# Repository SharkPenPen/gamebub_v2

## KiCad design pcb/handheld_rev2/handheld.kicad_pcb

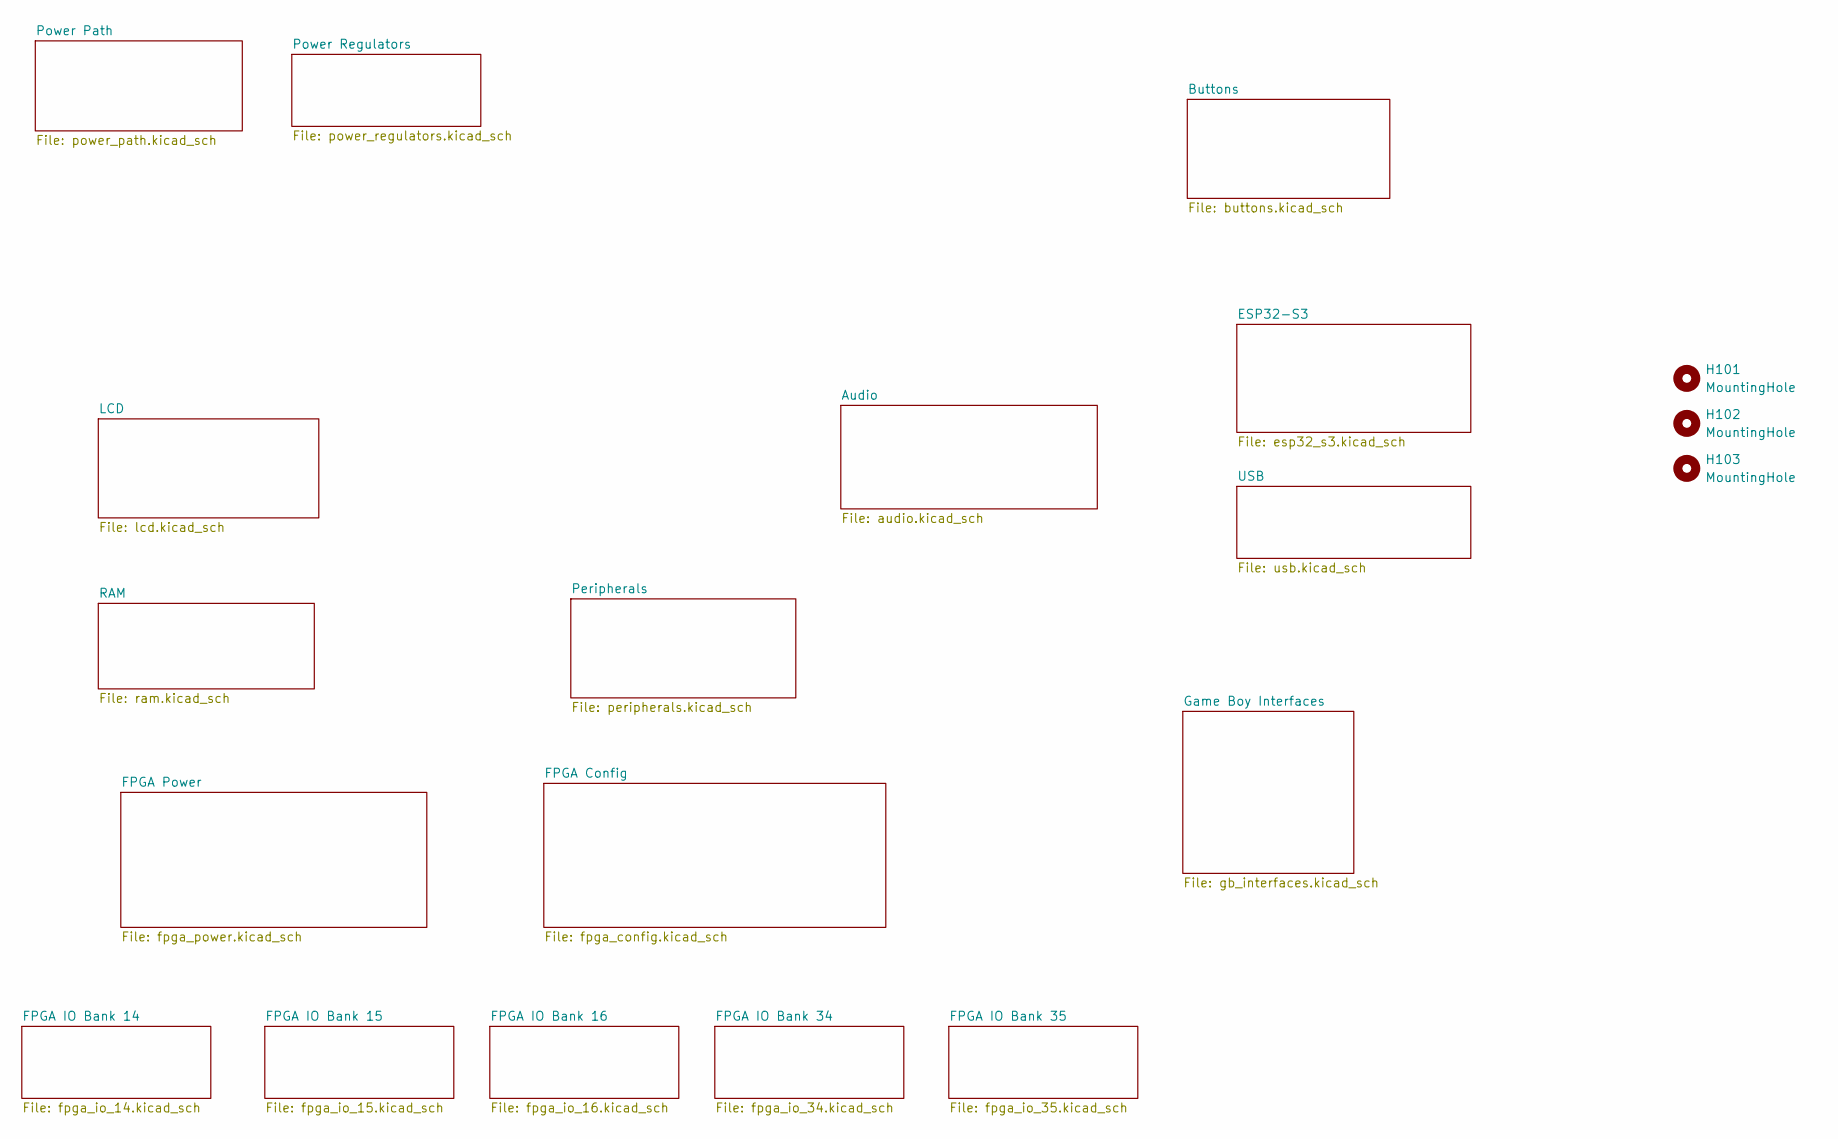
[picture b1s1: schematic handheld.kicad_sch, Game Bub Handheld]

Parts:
H101, H102, H103: MountingHole; MountingHole_2.7mm_M2.5

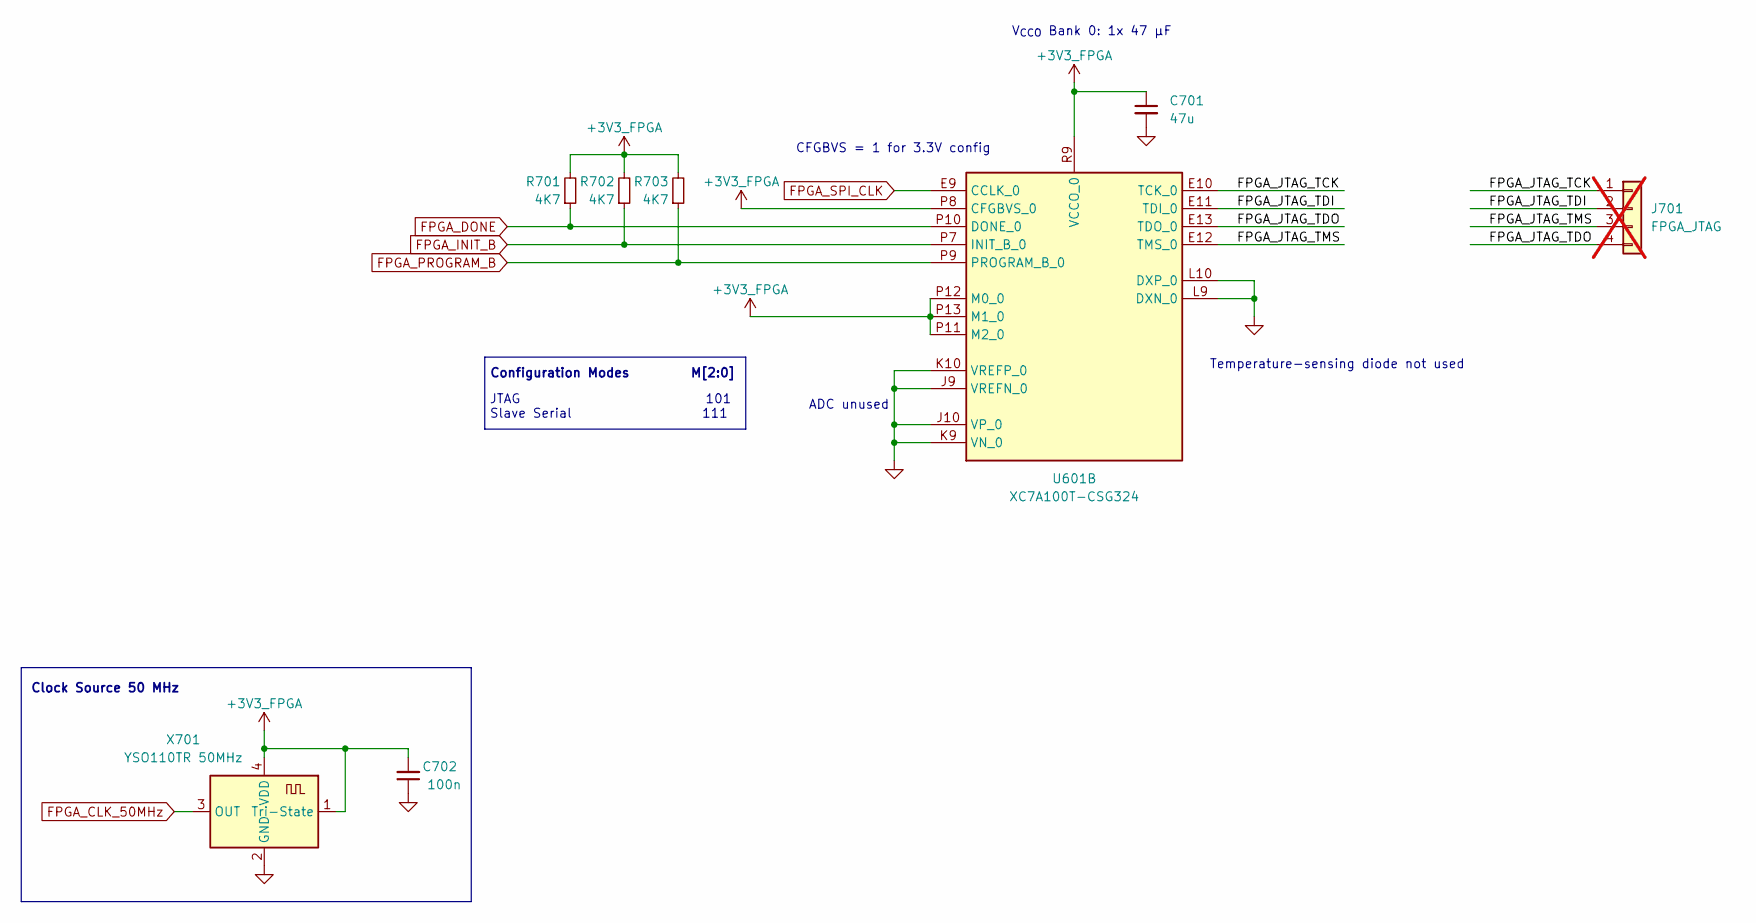
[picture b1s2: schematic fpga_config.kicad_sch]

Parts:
C701: 47u; C_0805_2012Metric; LCSC C16780
C702: 100n; C_0402_1005Metric; LCSC C1525
J701: FPGA_JTAG; PinSocket_1x04_P2.54mm_Vertical; not fitted
R701, R702, R703: 4K7; R_0402_1005Metric; LCSC C25900
U601: XC7A100T-CSG324; Xilinx_CSG324; LCSC C1521791
X701: YSO110TR 50MHz; Oscillator_SMD_SeikoEpson_SG8002CE-4Pin_3.2x2.5mm; LCSC C5203552

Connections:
+3V3_FPGA: C701.1, C702.2, R701.2, R702.2, R703.2, U601.P8 (CFGBVS_0), U601.P11 (M2_0), U601.P12 (M0_0), U601.P13 (M1_0), U601.R9 (VCCO_0), X701.1 (Tri-State), X701.4 (VDD); also elsewhere on the board
/FPGA Config/FPGA_JTAG_TCK: J701.1, U601.E10 (TCK_0)
/FPGA Config/FPGA_JTAG_TDI: J701.2, U601.E11 (TDI_0)
/FPGA Config/FPGA_JTAG_TDO: J701.4, U601.E13 (TDO_0)
/FPGA Config/FPGA_JTAG_TMS: J701.3, U601.E12 (TMS_0)
FPGA_CLK_50MHz: X701.3 (OUT); also elsewhere on the board
FPGA_DONE: R701.1, U601.P10 (DONE_0); also elsewhere on the board
FPGA_INIT_B: R702.1, U601.P7 (INIT_B_0); also elsewhere on the board
FPGA_PROGRAM_B: R703.1, U601.P9 (PROGRAM_B_0); also elsewhere on the board
FPGA_SPI_CLK: U601.E9 (CCLK_0); also elsewhere on the board
GND: C701.2, C702.1, U601.J9 (VREFN_0), U601.J10 (VP_0), U601.K9 (VN_0), U601.K10 (VREFP_0), U601.L9 (DXN_0), U601.L10 (DXP_0), X701.2 (GND); also elsewhere on the board

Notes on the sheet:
Clock Source 50 MHz
JTAG 101 Slave Serial 111
V_{CCO} Bank 0: 1x 47 µF
ADC unused
CFGBVS = 1 for 3.3V config
Temperature-sensing diode not used
Configuration Modes M[2:0]

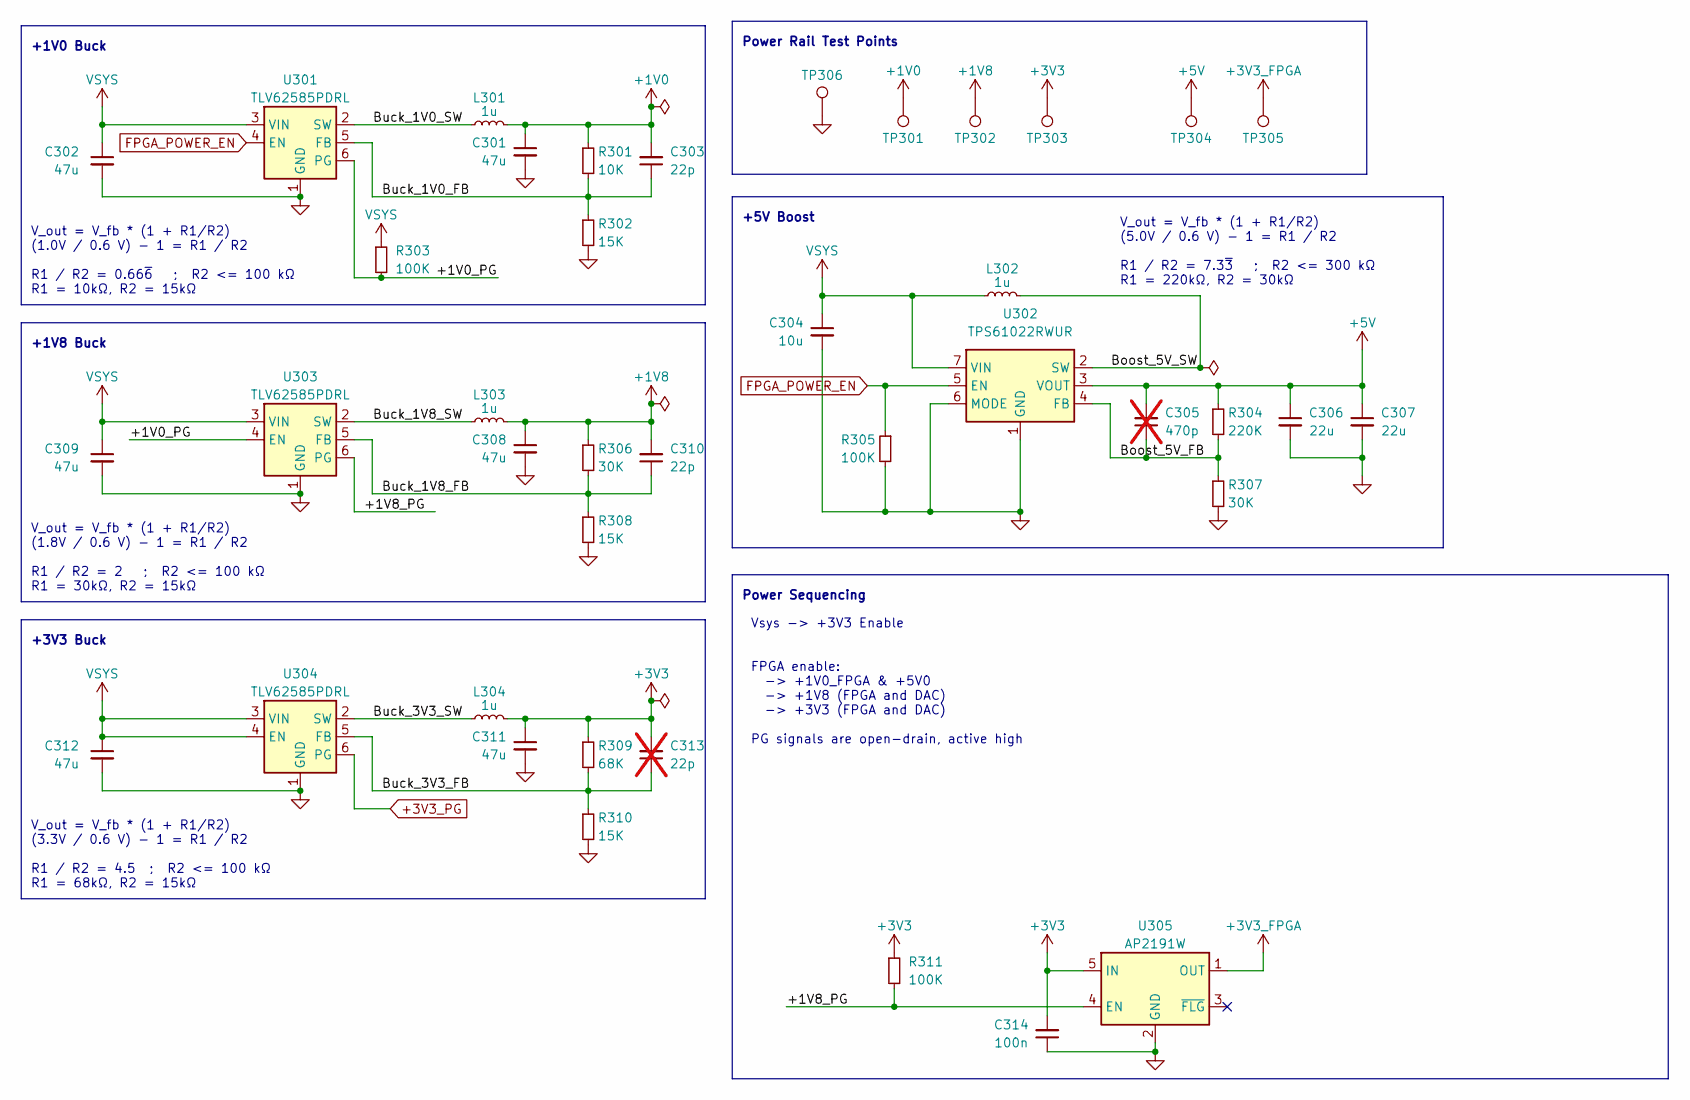
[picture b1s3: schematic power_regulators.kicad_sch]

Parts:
C301, C302, C308, C309, C311, C312: 47u; C_0805_2012Metric; LCSC C16780
C303, C310: 22p; C_0402_1005Metric; LCSC C1555
C304: 10u; C_0402_1005Metric; LCSC C15525
C305: 470p; C_0402_1005Metric; LCSC C1537; not fitted
C306, C307: 22u; C_0805_2012Metric; LCSC C45783
C313: 22p; C_0402_1005Metric; LCSC C1555; not fitted
C314: 100n; C_0402_1005Metric; LCSC C1525
L301, L302, L303, L304: 1u; L_Sunlord_SWPA252012S; LCSC C98348
R301: 10K; R_0402_1005Metric; LCSC C25744
R302, R308, R310: 15K; R_0402_1005Metric; LCSC C25756
R303, R305, R311: 100K; R_0402_1005Metric; LCSC C25741
R304: 220K; R_0603_1608Metric; LCSC C22961
R306, R307: 30K; R_0402_1005Metric; LCSC C25776
R309: 68K; R_0402_1005Metric; LCSC C36871
TP301: +1V0; TestPoint_2.54mm_THT
TP302: +1V8; TestPoint_2.54mm_THT
TP303: +3V3; TestPoint_2.54mm_THT
TP304: +5V; TestPoint_2.54mm_THT
TP305: +3V3_FPGA; TestPoint_2.54mm_THT
TP306: GND; TestPoint_2.54mm_THT
U301, U303, U304: TLV62585PDRL; SOT-563; LCSC C485118
U302: TPS61022RWUR; VQFN-7_L2.0-W2.0-P0.55-TL_RWU; LCSC C915088
U305: AP2191W; SOT-23-5; LCSC C141321

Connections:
+1V0: C301.1, C303.2, L301.2, R301.1, TP301.1; also elsewhere on the board
+1V8: C308.1, C310.2, L303.2, R306.1, TP302.1; also elsewhere on the board
+3V3: C311.1, C313.2, C314.2, L304.2, R309.1, R311.1, TP303.1, U305.5 (IN); also elsewhere on the board
+3V3_FPGA: TP305.1, U305.1 (OUT); also elsewhere on the board
+3V3_PG: U304.6 (PG); also elsewhere on the board
+5V: C305.2, C306.1, C307.1, R304.1, TP304.1, U302.3 (VOUT); also elsewhere on the board
/Power Regulators/+1V0_PG: R303.2, U301.6 (PG), U303.4 (EN)
/Power Regulators/+1V8_PG: R311.2, U303.6 (PG), U305.4 (EN)
/Power Regulators/Boost_5V_FB: C305.1, R304.2, R307.1, U302.4 (FB)
/Power Regulators/Boost_5V_SW: L302.2, U302.2 (SW)
/Power Regulators/Buck_1V0_FB: C303.1, R301.2, R302.1, U301.5 (FB)
/Power Regulators/Buck_1V0_SW: L301.1, U301.2 (SW)
/Power Regulators/Buck_1V8_FB: C310.1, R306.2, R308.1, U303.5 (FB)
/Power Regulators/Buck_1V8_SW: L303.1, U303.2 (SW)
/Power Regulators/Buck_3V3_FB: C313.1, R309.2, R310.1, U304.5 (FB)
/Power Regulators/Buck_3V3_SW: L304.1, U304.2 (SW)
FPGA_POWER_EN: R305.1, U301.4 (EN), U302.5 (EN); also elsewhere on the board
GND: C301.2, C302.2, C304.2, C306.2, C307.2, C308.2, C309.2, C311.2, C312.2, C314.1, R302.2, R305.2, R307.2, R308.2, R310.2, TP306.1, U301.1 (GND), U302.1 (GND), U302.6 (MODE), U303.1 (GND), U304.1 (GND), U305.2 (GND); also elsewhere on the board
VSYS: C302.1, C304.1, C309.1, C312.1, L302.1, R303.1, U301.3 (VIN), U302.7 (VIN), U303.3 (VIN), U304.3 (VIN), U304.4 (EN); also elsewhere on the board

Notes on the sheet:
+1V8 Buck
V_out = V_fb * (1 + R1/R2) (5.0V / 0.6 V) - 1 = R1 / R2 R1 / R2 = 7.3~{3} ; R2 <= 300 kΩ R1 = 220kΩ, R2 = 30kΩ
V_out = V_fb * (1 + R1/R2) (3.3V / 0.6 V) - 1 = R1 / R2 R1 / R2 = 4.5 ; R2 <= 100 kΩ R1 = 68kΩ, R2 = 15kΩ
+1V0 Buck
V_out = V_fb * (1 + R1/R2) (1.8V / 0.6 V) - 1 = R1 / R2 R1 / R2 = 2 ; R2 <= 100 kΩ R1 = 30kΩ, R2 = 15kΩ
Vsys -> +3V3 Enable FPGA enable: -> +1V0_FPGA & +5V0 -> +1V8 (FPGA and DAC) -> +3V3 (FPGA and DAC) PG signals are open-drain, active high
Power Rail Test Points
Power Sequencing
V_out = V_fb * (1 + R1/R2) (1.0V / 0.6 V) - 1 = R1 / R2 R1 / R2 = 0.66~{6} ; R2 <= 100 kΩ R1 = 10kΩ, R2 = 15kΩ
+3V3 Buck
+5V Boost

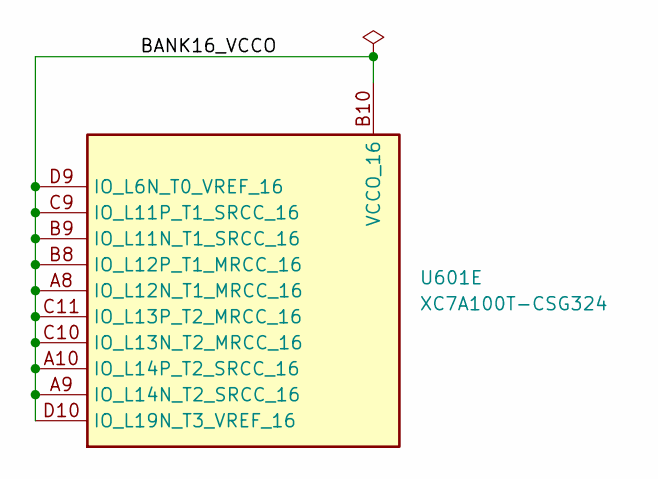
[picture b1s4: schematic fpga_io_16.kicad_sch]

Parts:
U601: XC7A100T-CSG324; Xilinx_CSG324; LCSC C1521791

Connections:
/FPGA IO Bank 16/BANK16_VCCO: U601.A8 (IO_L12N_T1_MRCC_16), U601.A9 (IO_L14N_T2_SRCC_16), U601.A10 (IO_L14P_T2_SRCC_16), U601.B8 (IO_L12P_T1_MRCC_16), U601.B9 (IO_L11N_T1_SRCC_16), U601.B10 (VCCO_16), U601.C9 (IO_L11P_T1_SRCC_16), U601.C10 (IO_L13N_T2_MRCC_16), U601.C11 (IO_L13P_T2_MRCC_16), U601.D9 (IO_L6N_T0_VREF_16), U601.D10 (IO_L19N_T3_VREF_16)

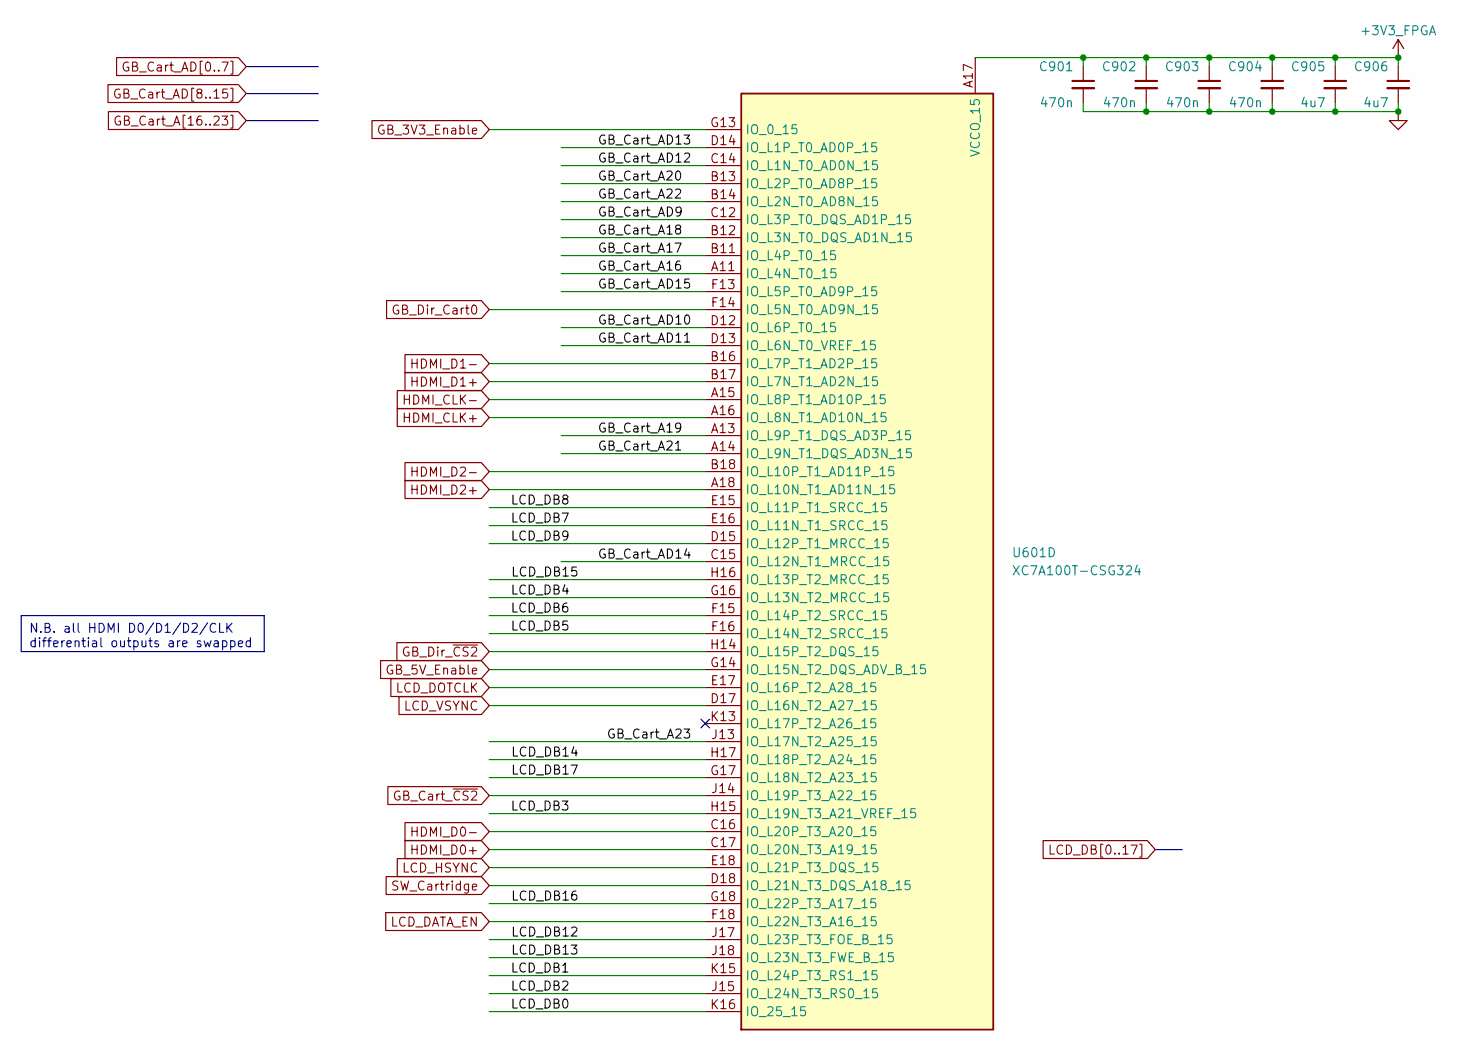
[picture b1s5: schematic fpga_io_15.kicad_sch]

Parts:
C901, C902, C903, C904: 470n; C_0402_1005Metric; LCSC C47339
C905, C906: 4u7; C_0402_1005Metric; LCSC C23733
U601: XC7A100T-CSG324; Xilinx_CSG324; LCSC C1521791

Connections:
+3V3_FPGA: C901.1, C902.1, C903.1, C904.1, C905.1, C906.1, U601.A17 (VCCO_15), U601.C13 (VCCO_15), U601.D16 (VCCO_15), U601.G15 (VCCO_15), U601.H18 (VCCO_15), U601.K14 (VCCO_15); also elsewhere on the board
GB_3V3_Enable: U601.G13 (IO_0_15); also elsewhere on the board
GB_5V_Enable: U601.G14 (IO_L15N_T2_DQS_ADV_B_15); also elsewhere on the board
GB_Cart_A16: U601.A11 (IO_L4N_T0_15); also elsewhere on the board
GB_Cart_A17: U601.B11 (IO_L4P_T0_15); also elsewhere on the board
GB_Cart_A18: U601.B12 (IO_L3N_T0_DQS_AD1N_15); also elsewhere on the board
GB_Cart_A19: U601.A13 (IO_L9P_T1_DQS_AD3P_15); also elsewhere on the board
GB_Cart_A20: U601.B13 (IO_L2P_T0_AD8P_15); also elsewhere on the board
GB_Cart_A21: U601.A14 (IO_L9N_T1_DQS_AD3N_15); also elsewhere on the board
GB_Cart_A22: U601.B14 (IO_L2N_T0_AD8N_15); also elsewhere on the board
GB_Cart_A23: U601.J13 (IO_L17N_T2_A25_15); also elsewhere on the board
GB_Cart_AD9: U601.C12 (IO_L3P_T0_DQS_AD1P_15); also elsewhere on the board
GB_Cart_AD10: U601.D12 (IO_L6P_T0_15); also elsewhere on the board
GB_Cart_AD11: U601.D13 (IO_L6N_T0_VREF_15); also elsewhere on the board
GB_Cart_AD12: U601.C14 (IO_L1N_T0_AD0N_15); also elsewhere on the board
GB_Cart_AD13: U601.D14 (IO_L1P_T0_AD0P_15); also elsewhere on the board
GB_Cart_AD14: U601.C15 (IO_L12N_T1_MRCC_15); also elsewhere on the board
GB_Cart_AD15: U601.F13 (IO_L5P_T0_AD9P_15); also elsewhere on the board
GB_Cart_~CS2: U601.J14 (IO_L19P_T3_A22_15); also elsewhere on the board
GB_Dir_Cart0: U601.F14 (IO_L5N_T0_AD9N_15); also elsewhere on the board
GB_Dir_~CS2: U601.H14 (IO_L15P_T2_DQS_15); also elsewhere on the board
GND: C901.2, C902.2, C903.2, C904.2, C905.2, C906.2; also elsewhere on the board
HDMI_CLK+: U601.A16 (IO_L8N_T1_AD10N_15); also elsewhere on the board
HDMI_CLK-: U601.A15 (IO_L8P_T1_AD10P_15); also elsewhere on the board
HDMI_D0+: U601.C17 (IO_L20N_T3_A19_15); also elsewhere on the board
HDMI_D0-: U601.C16 (IO_L20P_T3_A20_15); also elsewhere on the board
HDMI_D1+: U601.B17 (IO_L7N_T1_AD2N_15); also elsewhere on the board
HDMI_D1-: U601.B16 (IO_L7P_T1_AD2P_15); also elsewhere on the board
HDMI_D2+: U601.A18 (IO_L10N_T1_AD11N_15); also elsewhere on the board
HDMI_D2-: U601.B18 (IO_L10P_T1_AD11P_15); also elsewhere on the board
LCD_DATA_EN: U601.F18 (IO_L22N_T3_A16_15); also elsewhere on the board
LCD_DB0: U601.K16 (IO_25_15); also elsewhere on the board
LCD_DB1: U601.K15 (IO_L24P_T3_RS1_15); also elsewhere on the board
LCD_DB2: U601.J15 (IO_L24N_T3_RS0_15); also elsewhere on the board
LCD_DB3: U601.H15 (IO_L19N_T3_A21_VREF_15); also elsewhere on the board
LCD_DB4: U601.G16 (IO_L13N_T2_MRCC_15); also elsewhere on the board
LCD_DB5: U601.F16 (IO_L14N_T2_SRCC_15); also elsewhere on the board
LCD_DB6: U601.F15 (IO_L14P_T2_SRCC_15); also elsewhere on the board
LCD_DB7: U601.E16 (IO_L11N_T1_SRCC_15); also elsewhere on the board
LCD_DB8: U601.E15 (IO_L11P_T1_SRCC_15); also elsewhere on the board
LCD_DB9: U601.D15 (IO_L12P_T1_MRCC_15); also elsewhere on the board
LCD_DB12: U601.J17 (IO_L23P_T3_FOE_B_15); also elsewhere on the board
LCD_DB13: U601.J18 (IO_L23N_T3_FWE_B_15); also elsewhere on the board
LCD_DB14: U601.H17 (IO_L18P_T2_A24_15); also elsewhere on the board
LCD_DB15: U601.H16 (IO_L13P_T2_MRCC_15); also elsewhere on the board
LCD_DB16: U601.G18 (IO_L22P_T3_A17_15); also elsewhere on the board
LCD_DB17: U601.G17 (IO_L18N_T2_A23_15); also elsewhere on the board
LCD_DOTCLK: U601.E17 (IO_L16P_T2_A28_15); also elsewhere on the board
LCD_HSYNC: U601.E18 (IO_L21P_T3_DQS_15); also elsewhere on the board
LCD_VSYNC: U601.D17 (IO_L16N_T2_A27_15); also elsewhere on the board
SW_Cartridge: U601.D18 (IO_L21N_T3_DQS_A18_15); also elsewhere on the board

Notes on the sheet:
N.B. all HDMI D0/D1/D2/CLK differential outputs are swapped

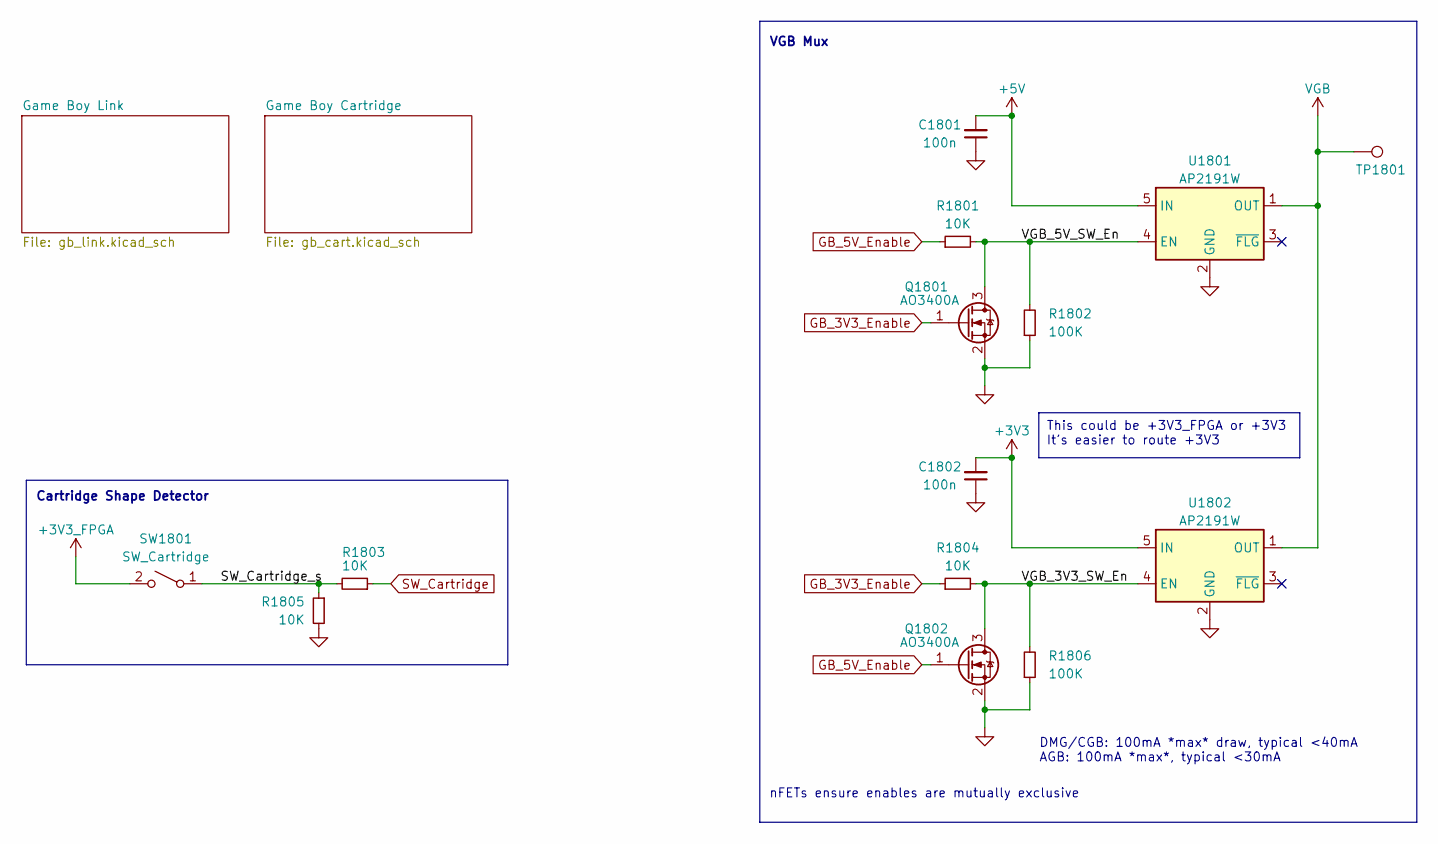
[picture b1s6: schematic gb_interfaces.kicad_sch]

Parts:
C1801, C1802: 100n; C_0402_1005Metric; LCSC C1525
Q1801, Q1802: AO3400A; SOT-23; LCSC C20917
R1801, R1803, R1804, R1805: 10K; R_0402_1005Metric; LCSC C25744
R1802, R1806: 100K; R_0402_1005Metric; LCSC C25741
SW1801: SW_Cartridge; JJOV0UL650NONPRBK_SIDE
TP1801: VGB; TestPoint_2.54mm_THT
U1801, U1802: AP2191W; SOT-23-5; LCSC C141321

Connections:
+3V3: C1802.2, U1802.5 (IN); also elsewhere on the board
+3V3_FPGA: SW1801.2 (B); also elsewhere on the board
+5V: C1801.2, U1801.5 (IN); also elsewhere on the board
/Game Boy Interfaces/SW_Cartridge_s: R1803.2, R1805.1, SW1801.1 (A)
/Game Boy Interfaces/VGB_3V3_SW_En: Q1802.3 (D), R1804.2, R1806.2, U1802.4 (EN)
/Game Boy Interfaces/VGB_5V_SW_En: Q1801.3 (D), R1801.2, R1802.2, U1801.4 (EN)
GB_3V3_Enable: Q1801.1 (G), R1804.1; also elsewhere on the board
GB_5V_Enable: Q1802.1 (G), R1801.1; also elsewhere on the board
GND: C1801.1, C1802.1, Q1801.2 (S), Q1802.2 (S), R1802.1, R1805.2, R1806.1, U1801.2 (GND), U1802.2 (GND); also elsewhere on the board
SW_Cartridge: R1803.1; also elsewhere on the board
VGB: TP1801.1, U1801.1 (OUT), U1802.1 (OUT); also elsewhere on the board

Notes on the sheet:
This could be +3V3_FPGA or +3V3 It's easier to route +3V3
DMG/CGB: 100mA *max* draw, typical <40mA AGB: 100mA *max*, typical <30mA
Cartridge Shape Detector
VGB Mux
nFETs ensure enables are mutually exclusive

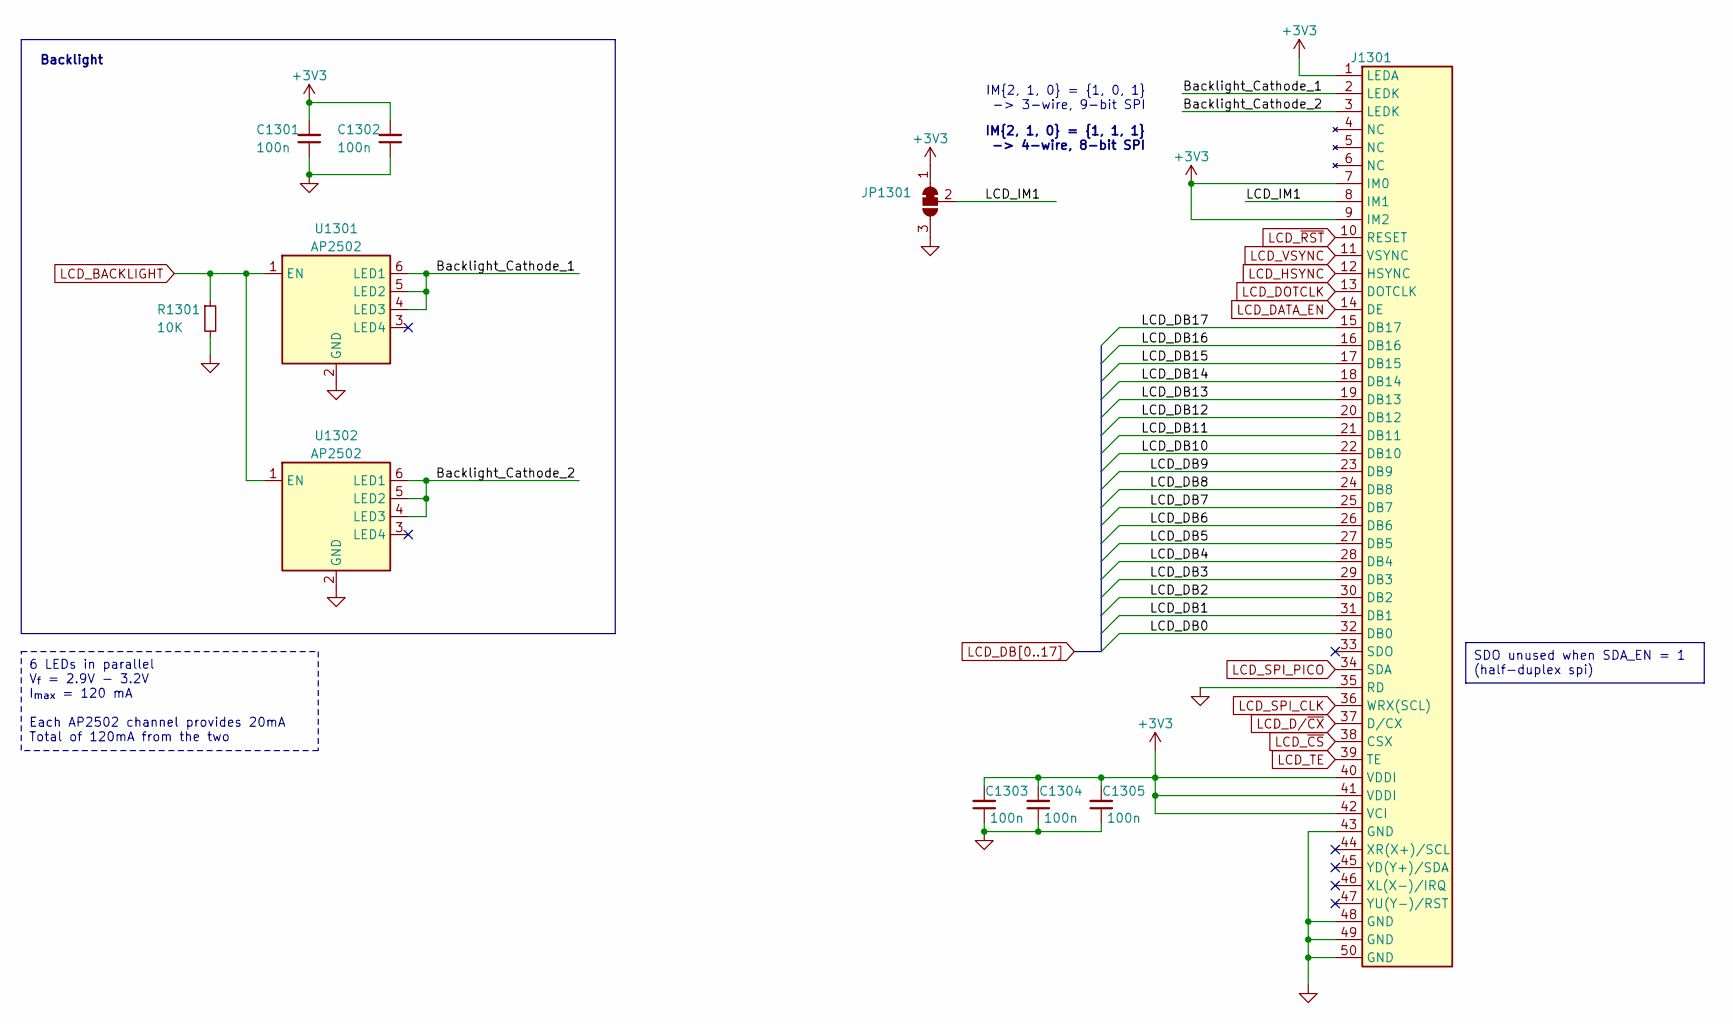
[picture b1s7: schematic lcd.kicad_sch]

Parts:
C1301, C1302, C1303, C1304, C1305: 100n; C_0402_1005Metric; LCSC C1525
J1301: Hirose_FH12S-50S-0.5SH_1x50-1MP_P0.50mm_Horizontal_FLIPPED; LCSC C598003
JP1301: SolderJumper_3_Bridged12; SolderJumper-3_P1.3mm_Bridged12_RoundedPad1.0x1.5mm
R1301: 10K; R_0402_1005Metric; LCSC C25744
U1301, U1302: AP2502; SOT-23-6; LCSC C460349

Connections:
+3V3: C1301.2, C1302.2, C1303.2, C1304.2, C1305.2, J1301.1 (LEDA), J1301.7 (IM0), J1301.9 (IM2), J1301.40 (VDDI), J1301.41 (VDDI), J1301.42 (VCI), JP1301.1 (A); also elsewhere on the board
/LCD/Backlight_Cathode_1: J1301.2 (LEDK), U1301.4 (LED3), U1301.5 (LED2), U1301.6 (LED1)
/LCD/Backlight_Cathode_2: J1301.3 (LEDK), U1302.4 (LED3), U1302.5 (LED2), U1302.6 (LED1)
/LCD/LCD_IM1: J1301.8 (IM1), JP1301.2 (C)
GND: C1301.1, C1302.1, C1303.1, C1304.1, C1305.1, J1301.35 (RD), J1301.43 (GND), J1301.48 (GND), J1301.49 (GND), J1301.50 (GND), JP1301.3 (B), R1301.2, U1301.2 (GND), U1302.2 (GND); also elsewhere on the board
LCD_BACKLIGHT: R1301.1, U1301.1 (EN), U1302.1 (EN); also elsewhere on the board
LCD_DATA_EN: J1301.14 (DE); also elsewhere on the board
LCD_DB0: J1301.32 (DB0); also elsewhere on the board
LCD_DB1: J1301.31 (DB1); also elsewhere on the board
LCD_DB2: J1301.30 (DB2); also elsewhere on the board
LCD_DB3: J1301.29 (DB3); also elsewhere on the board
LCD_DB4: J1301.28 (DB4); also elsewhere on the board
LCD_DB5: J1301.27 (DB5); also elsewhere on the board
LCD_DB6: J1301.26 (DB6); also elsewhere on the board
LCD_DB7: J1301.25 (DB7); also elsewhere on the board
LCD_DB8: J1301.24 (DB8); also elsewhere on the board
LCD_DB9: J1301.23 (DB9); also elsewhere on the board
LCD_DB10: J1301.22 (DB10); also elsewhere on the board
LCD_DB11: J1301.21 (DB11); also elsewhere on the board
LCD_DB12: J1301.20 (DB12); also elsewhere on the board
LCD_DB13: J1301.19 (DB13); also elsewhere on the board
LCD_DB14: J1301.18 (DB14); also elsewhere on the board
LCD_DB15: J1301.17 (DB15); also elsewhere on the board
LCD_DB16: J1301.16 (DB16); also elsewhere on the board
LCD_DB17: J1301.15 (DB17); also elsewhere on the board
LCD_DOTCLK: J1301.13 (DOTCLK); also elsewhere on the board
LCD_D/~CX: J1301.37 (D/CX); also elsewhere on the board
LCD_HSYNC: J1301.12 (HSYNC); also elsewhere on the board
LCD_SPI_CLK: J1301.36 (WRX(SCL)); also elsewhere on the board
LCD_SPI_PICO: J1301.34 (SDA); also elsewhere on the board
LCD_TE: J1301.39 (TE); also elsewhere on the board
LCD_VSYNC: J1301.11 (VSYNC); also elsewhere on the board
LCD_~CS: J1301.38 (CSX); also elsewhere on the board
LCD_~RST: J1301.10 (RESET); also elsewhere on the board

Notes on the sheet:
SDO unused when SDA_EN = 1 (half-duplex spi)
6 LEDs in parallel V_{f} = 2.9V - 3.2V I_{max} = 120 mA Each AP2502 channel provides 20mA Total of 120mA from the two
Backlight
IM{2, 1, 0} = {1, 1, 1} -> 4-wire, 8-bit SPI
IM{2, 1, 0} = {1, 0, 1} -> 3-wire, 9-bit SPI

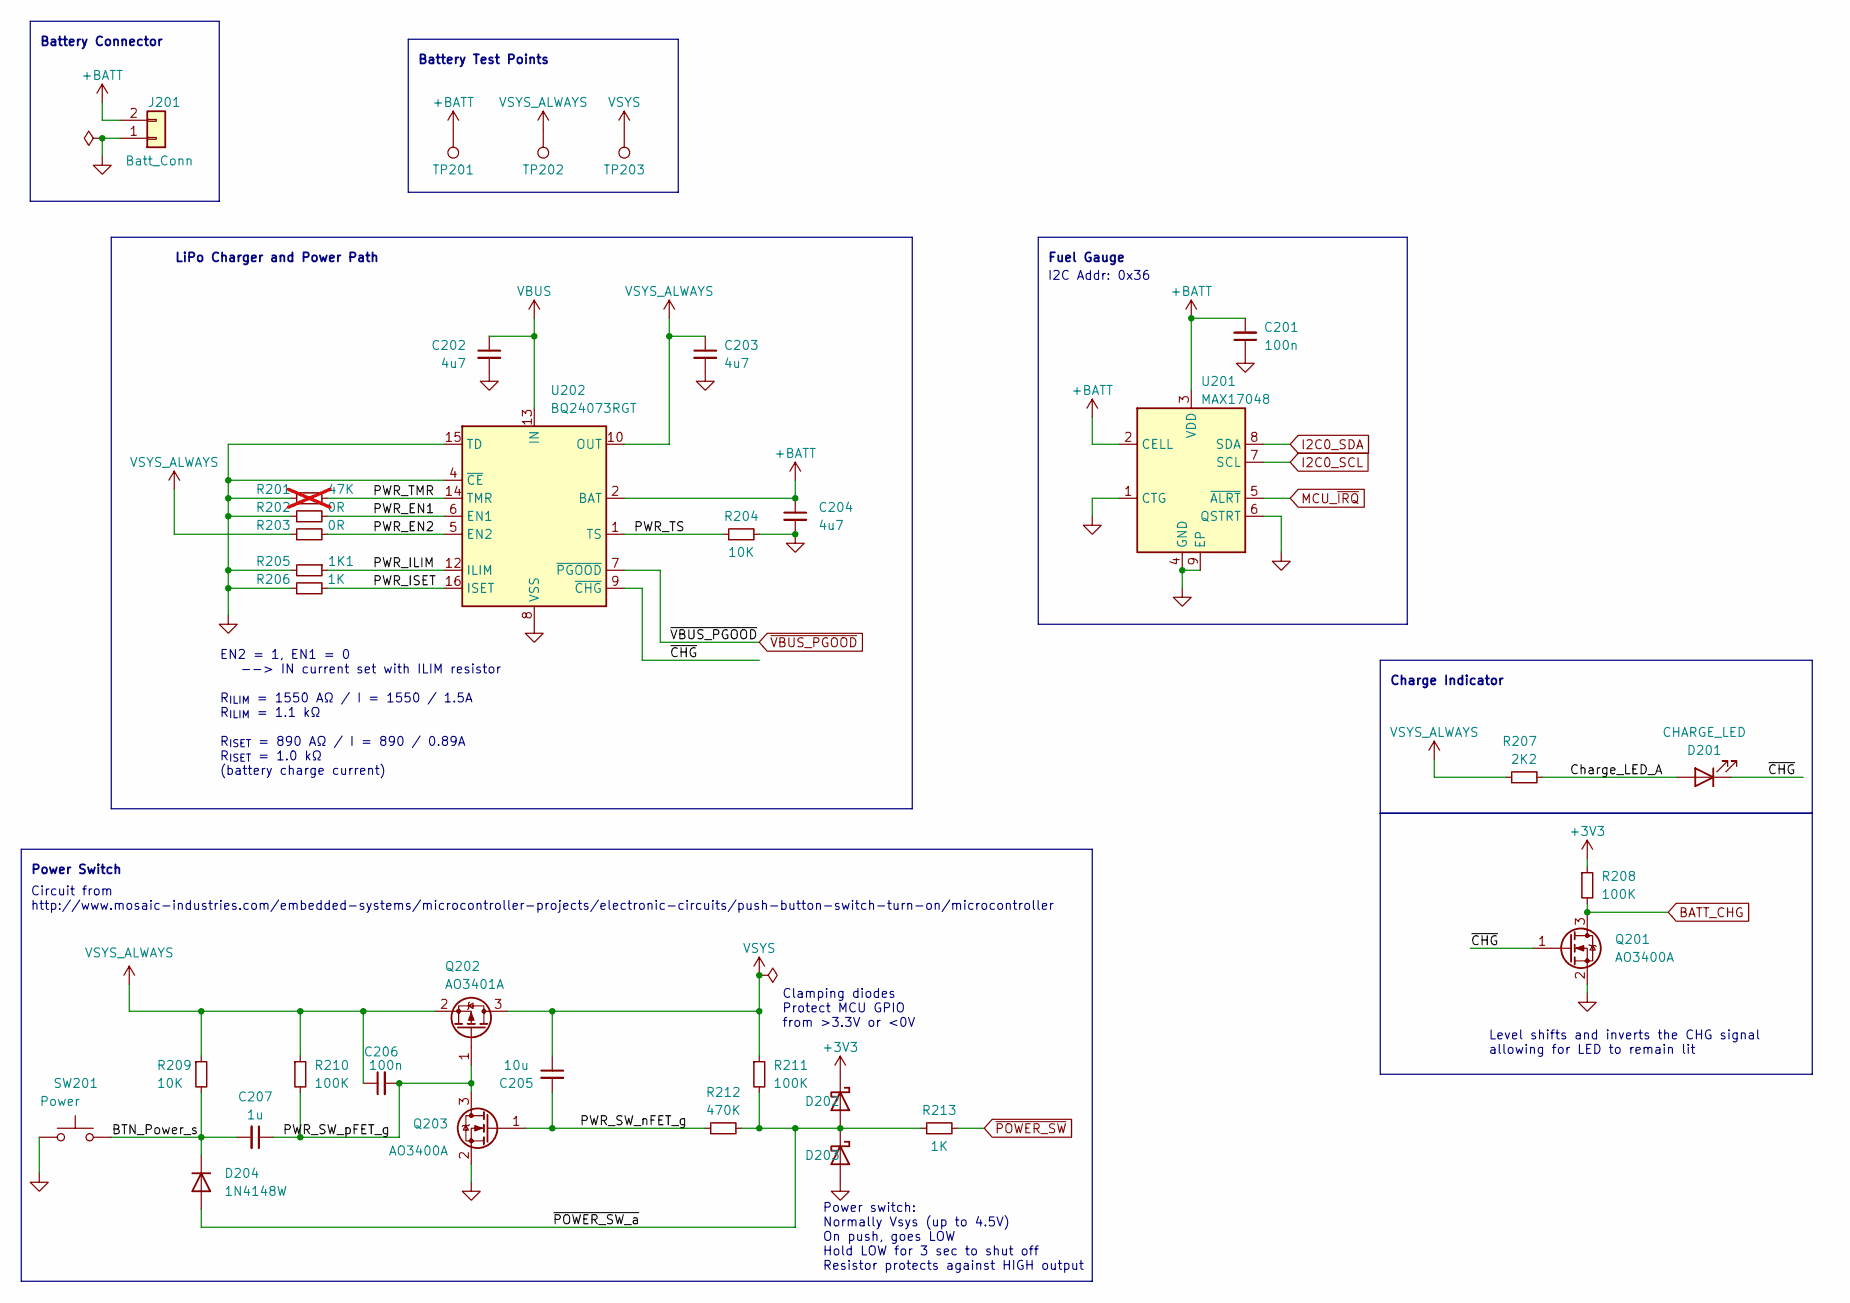
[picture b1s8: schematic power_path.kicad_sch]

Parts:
C201, C206: 100n; C_0402_1005Metric; LCSC C1525
C202, C203, C204: 4u7; C_0402_1005Metric; LCSC C23733
C205: 10u; C_0402_1005Metric; LCSC C15525
C207: 1u; C_0402_1005Metric; LCSC C52923
D201: CHARGE_LED; LED_0805_2012Metric; LCSC C2296
D202, D203: D_Schottky; D_SOD-323; LCSC C191023
D204: 1N4148W; D_SOD-123; LCSC C81598
J201: Batt_Conn; JST_PH_S2B-PH-SM4-TB_1x02-1MP_P2.00mm_Horizontal
Q201, Q203: AO3400A; SOT-23; LCSC C20917
Q202: AO3401A; SOT-23; LCSC C15127
R201: 47K; R_0402_1005Metric_Pad0.72x0.64mm_HandSolder; LCSC C25792; not fitted
R202, R203: 0R; R_0402_1005Metric_Pad0.72x0.64mm_HandSolder; LCSC C17168
R204, R209: 10K; R_0402_1005Metric; LCSC C25744
R205: 1K1; R_0402_1005Metric_Pad0.72x0.64mm_HandSolder; LCSC C25860
R206: 1K; R_0402_1005Metric_Pad0.72x0.64mm_HandSolder; LCSC C11702
R207: 2K2; R_0402_1005Metric; LCSC C25879
R208, R210, R211: 100K; R_0402_1005Metric; LCSC C25741
R212: 470K; R_0603_1608Metric_Pad0.98x0.95mm_HandSolder; LCSC C23178
R213: 1K; R_0402_1005Metric; LCSC C11702
SW201: Power; SW_SPST_SKSC; LCSC C115361
TP201: +BATT; TestPoint_2.54mm_THT
TP202: VSYS_ALWAYS; TestPoint_2.54mm_THT
TP203: VSYS; TestPoint_2.54mm_THT
U201: MAX17048; TDFN-8-1EP_2x2mm_P0.5mm_EP0.8x1.2mm; LCSC C2682616
U202: BQ24073RGT; VQFN-16-1EP_3x3mm_P0.5mm_EP1.6x1.6mm; LCSC C15220

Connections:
+3V3: D202.1 (K), R208.1; also elsewhere on the board
+BATT: C201.2, C204.1, J201.2, TP201.1, U201.2 (CELL), U201.3 (VDD), U202.2 (BAT), U202.3 (BAT)
/Power Path/BTN_Power_s: C207.2, D204.1 (K), R209.2, SW201.1
/Power Path/Charge_LED_A: D201.2 (A), R207.2
/Power Path/PWR_EN1: R202.2, U202.6 (EN1)
/Power Path/PWR_EN2: R203.2, U202.5 (EN2)
/Power Path/PWR_ILIM: R205.1, U202.12 (ILIM)
/Power Path/PWR_ISET: R206.2, U202.16 (ISET)
/Power Path/PWR_SW_nFET_g: C205.2, Q203.1 (G), R212.1
/Power Path/PWR_SW_pFET_g: C206.2, C207.1, Q202.1 (G), Q203.3 (D), R210.2
/Power Path/PWR_TMR: R201.1, U202.14 (TMR)
/Power Path/PWR_TS: R204.1, U202.1 (TS)
/Power Path/~CHG: D201.1 (K), Q201.1 (G), U202.9 (~CHG)
/Power Path/~POWER_SW_a: D202.2 (A), D203.1 (K), D204.2 (A), R211.2, R212.2, R213.1
BATT_CHG: Q201.3 (D), R208.2; also elsewhere on the board
GND: C201.1, C202.2, C203.2, C204.2, D203.2 (A), J201.1, Q201.2 (S), Q203.2 (S), R201.2, R202.1, R204.2, R205.2, R206.1, SW201.2, U201.1 (CTG), U201.4 (GND), U201.6 (QSTRT), U201.9 (EP), U202.4 (~CE), U202.8 (VSS), U202.15 (TD), U202.17 (VSS); also elsewhere on the board
I2C0_SCL: U201.7 (SCL); also elsewhere on the board
I2C0_SDA: U201.8 (SDA); also elsewhere on the board
MCU_~IRQ: U201.5 (~ALRT); also elsewhere on the board
VBUS: C202.1, U202.13 (IN); also elsewhere on the board
VSYS: C205.1, Q202.3 (D), R211.1, TP203.1; also elsewhere on the board
VSYS_ALWAYS: C203.1, C206.1, Q202.2 (S), R203.1, R207.1, R209.1, R210.1, TP202.1, U202.10 (OUT), U202.11 (OUT); also elsewhere on the board
~POWER_SW: R213.2; also elsewhere on the board
~VBUS_PGOOD: U202.7 (~PGOOD); also elsewhere on the board

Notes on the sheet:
Charge Indicator
Battery Connector
LiPo Charger and Power Path
Power Switch
Level shifts and inverts the CHG signal allowing for LED to remain lit
Battery Test Points
Power switch: Normally Vsys (up to 4.5V) On push, goes LOW Hold LOW for 3 sec to shut off Resistor protects against HIGH output
Clamping diodes Protect MCU GPIO from >3.3V or <0V
Circuit from http://www.mosaic-industries.com/embedded-systems/microcontroller-projects/electronic-circuits/push-button-switch-turn-on/microcontroller
I2C Addr: 0x36
EN2 = 1, EN1 = 0 --> IN current set with ILIM resistor R_{ILIM} = 1550 AΩ / I = 1550 / 1.5A R_{ILIM} = 1.1 kΩ R_{ISET} = 890 AΩ / I = 890 / 0.89A R_{ISET} = 1.0 kΩ (battery charge current)
Fuel Gauge
